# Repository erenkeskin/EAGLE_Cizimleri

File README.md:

# EAGLE_Cizimleri
AutoDesk Eagle PCB çizim programı ile çizdiğim çizimleri derlediğim depo

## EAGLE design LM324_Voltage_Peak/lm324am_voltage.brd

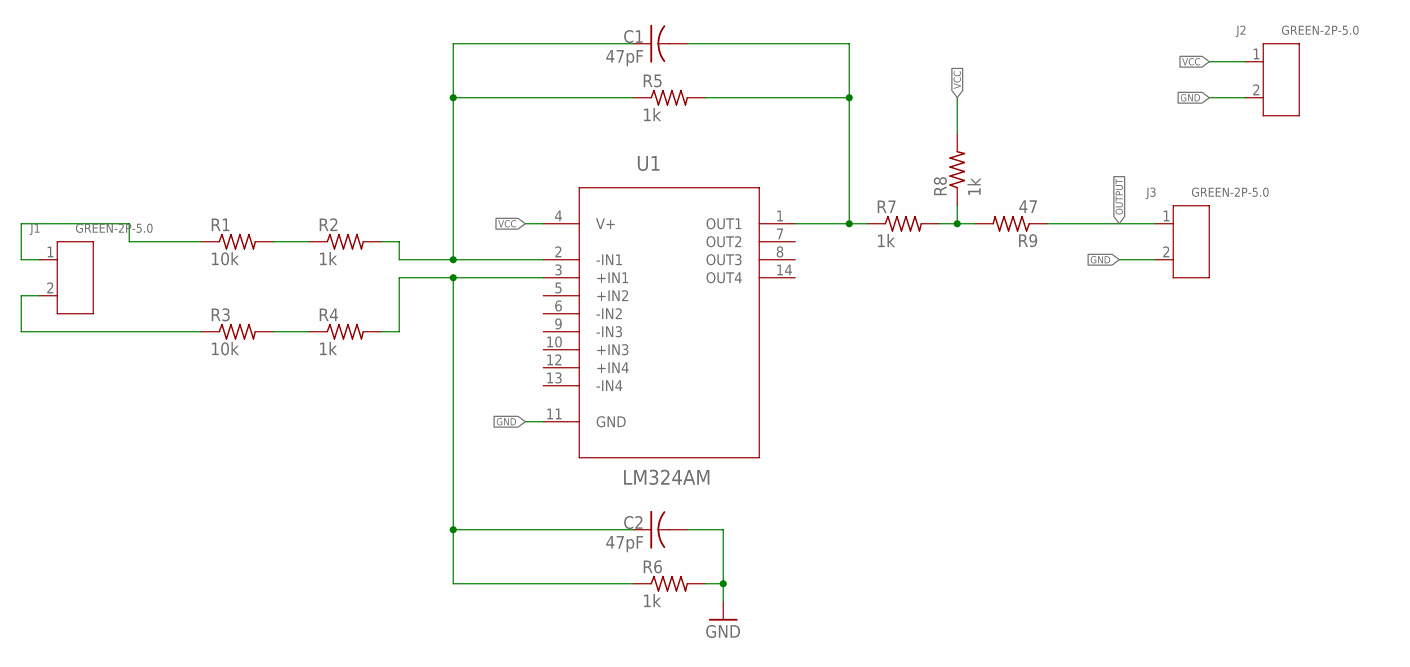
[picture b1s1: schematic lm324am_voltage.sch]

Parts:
C1, C2: 47pF; C1206
J1, J2, J3: GREEN-2P-5.0; H2-5.0-10.5X8.0MM
R1, R3: 10k; M1206
R2, R4, R5, R6, R7, R8: 1k; M1206
R9: 47; M1206
U1: LM324AM; SOIC127P620X175-14N

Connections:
GND: C2.2, J2.2, J3.2, R6.2, U1.11 (GND)
unnamed: J1.2, R3.1
unnamed: R3.2, R4.1
unnamed: R1.2, R2.1
unnamed: C1.1, R2.2, R5.1, U1.2 (-IN1)
unnamed: C2.1, R4.2, R6.1, U1.3 (+IN1)
unnamed: C1.2, R5.2, R7.1, U1.1 (OUT1)
unnamed: R7.2, R8.1, R9.2
unnamed: J1.1, R1.1
OUTPUT: J3.1, R9.1
VCC: J2.1, R8.2, U1.4 (V+)

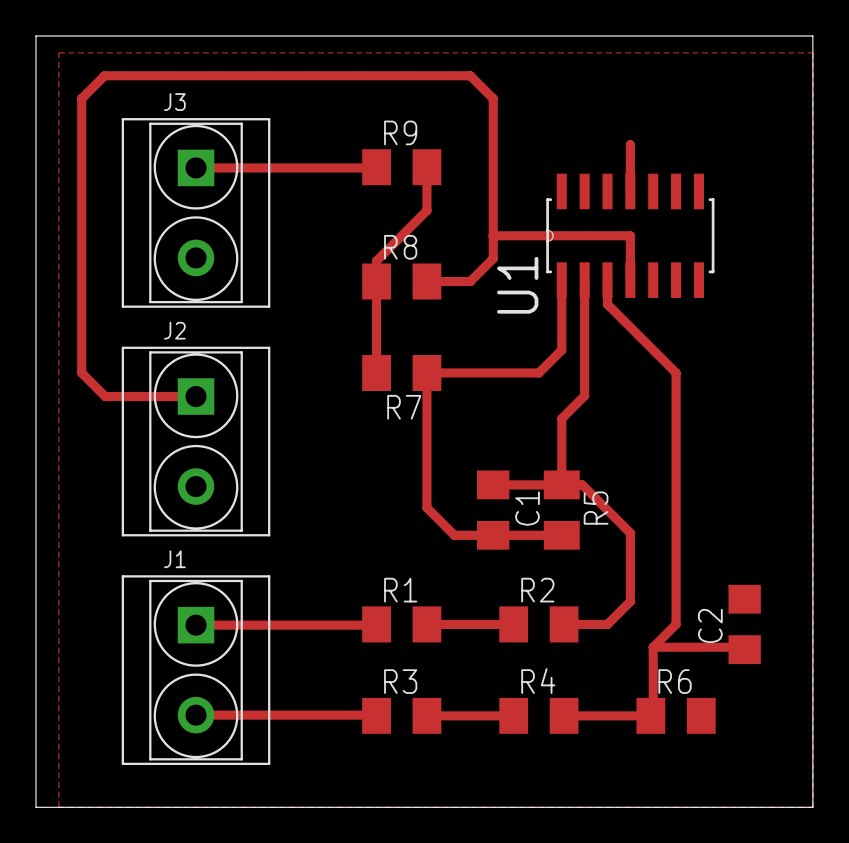
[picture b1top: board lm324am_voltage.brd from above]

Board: 2 copper layers, 43.2 x 42.9 mm, 15 parts (0 on the bottom side), 11 nets.

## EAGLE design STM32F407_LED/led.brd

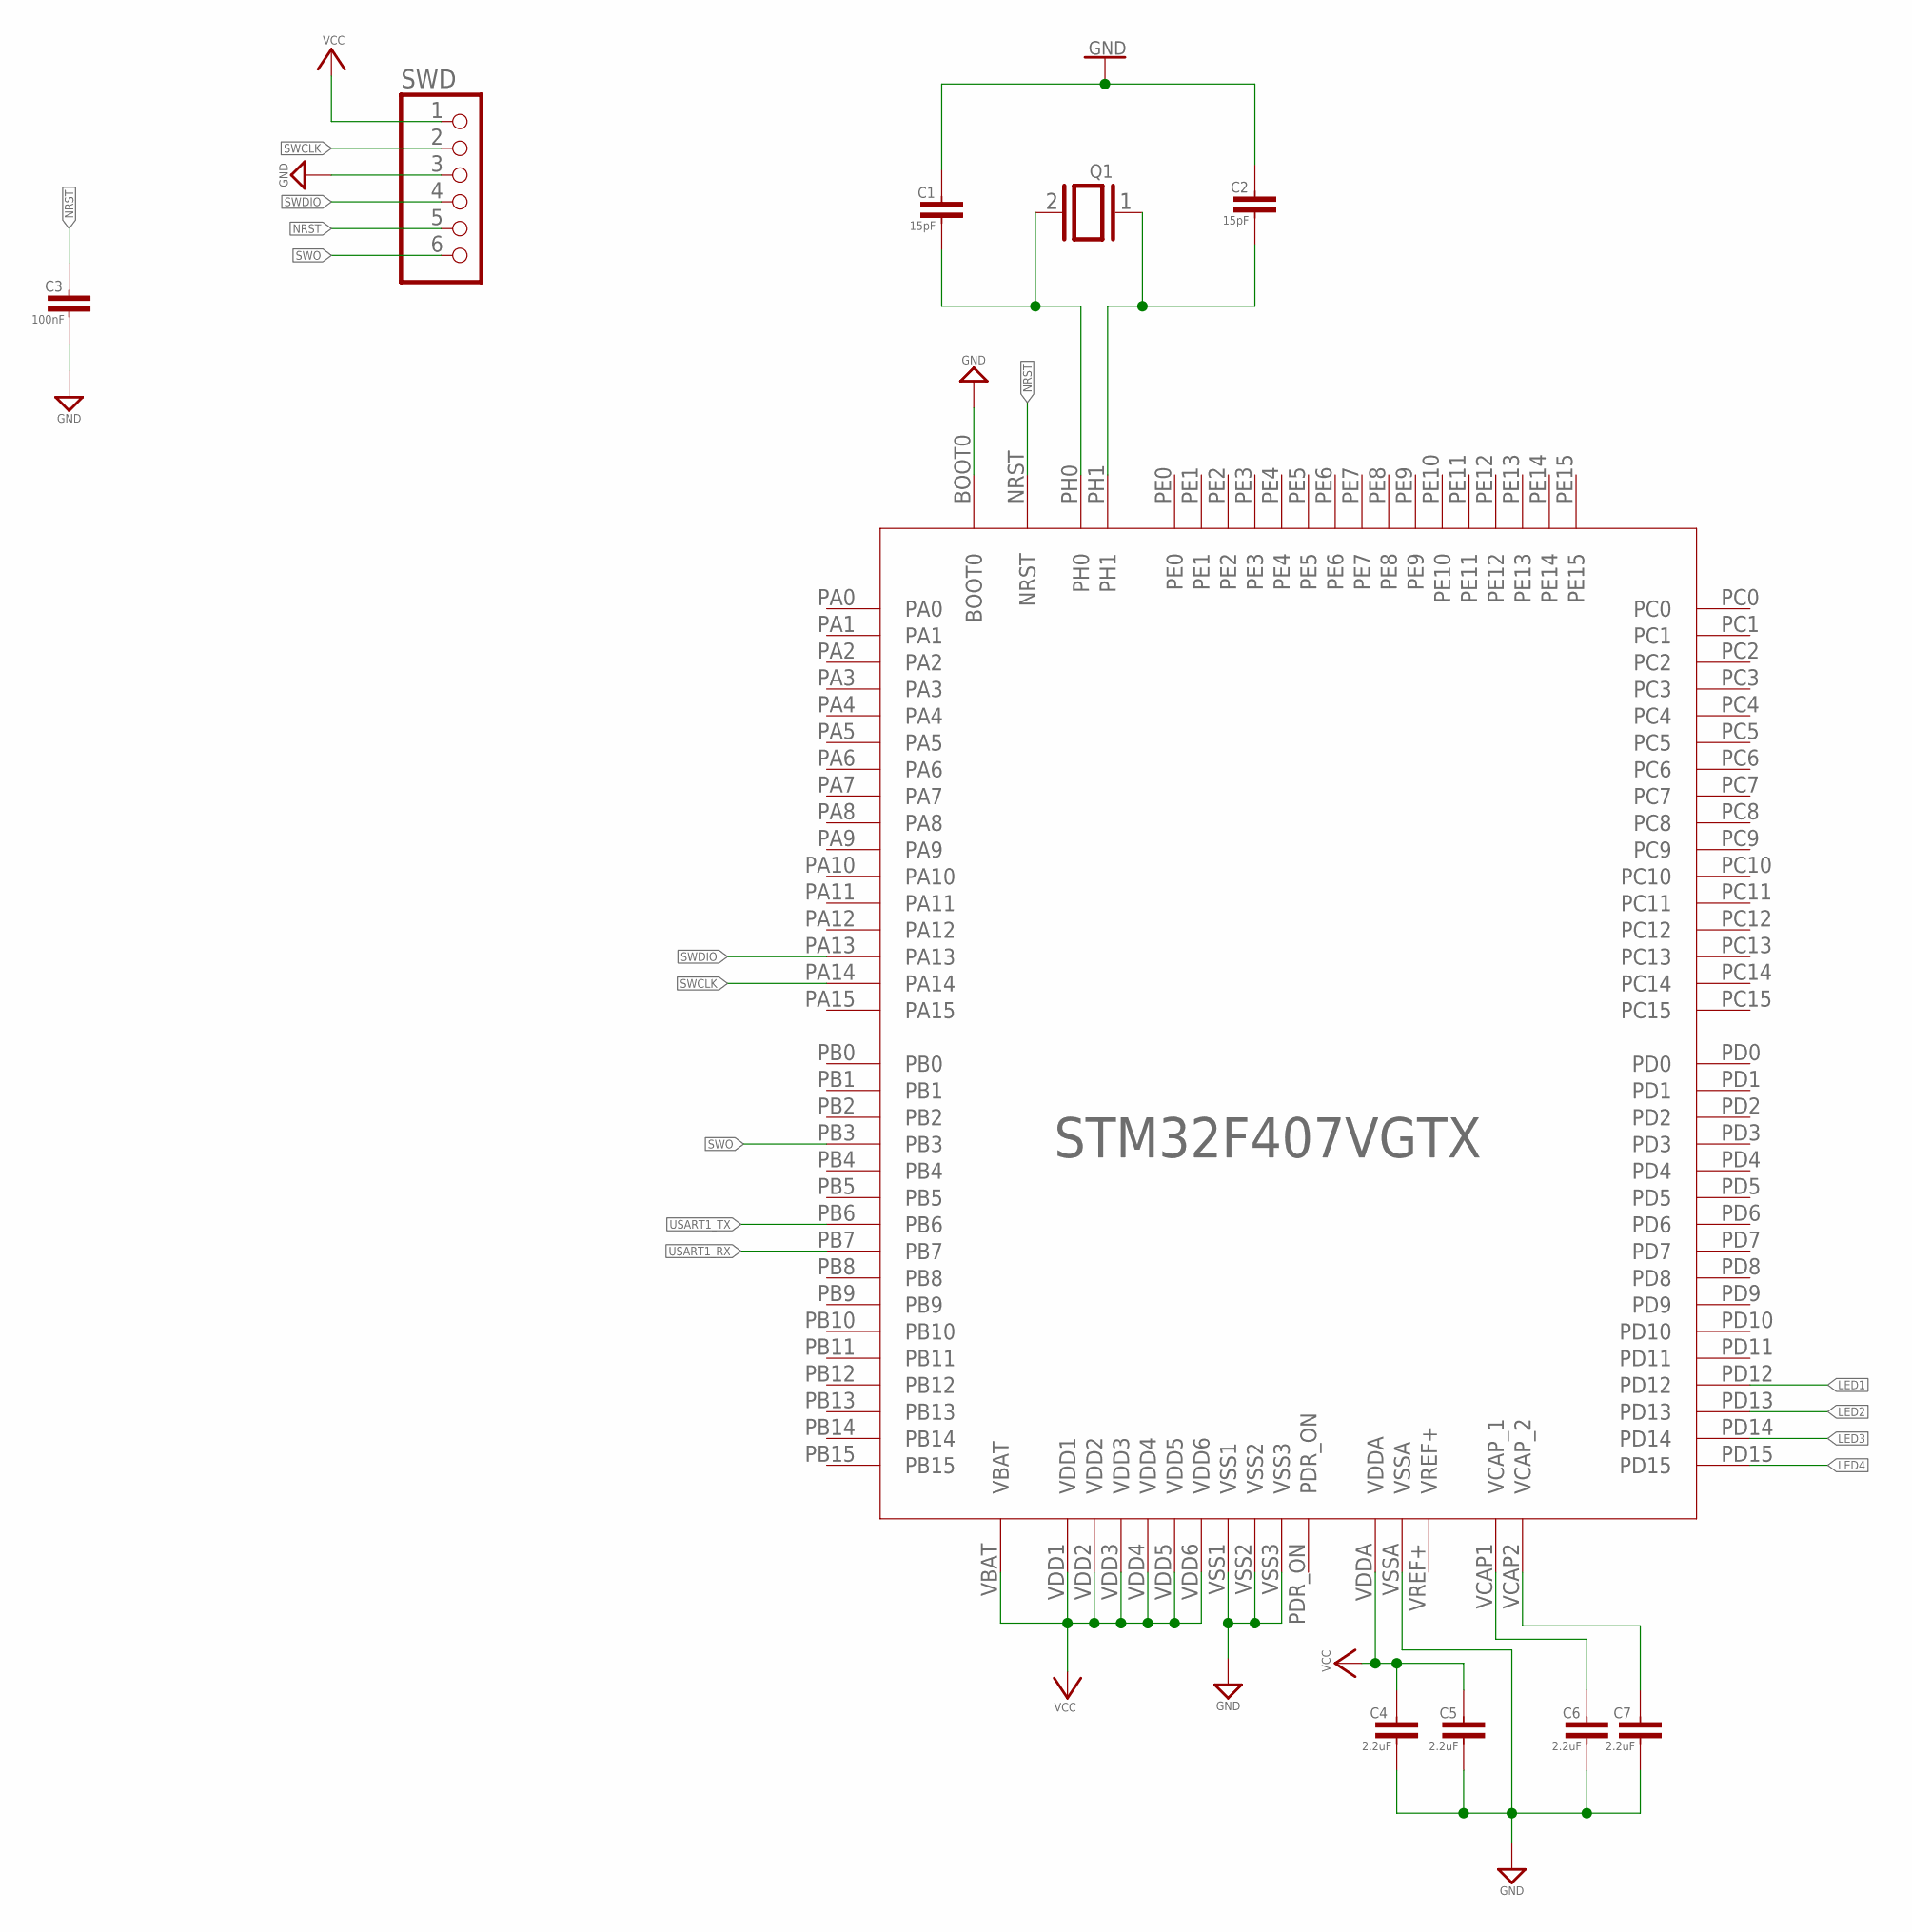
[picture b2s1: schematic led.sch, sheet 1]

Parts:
C1, C2: 15pF; C0603
C3: 100nF; C0603
C4, C5, C6, C7: 2.2uF; C0603
IC1: STM32F407VGTx; LQFP100
Q1: XTAL/S; QS
SWD: PINHD-1X6CB; 1X06-CLEANBIG

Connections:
GND: C1.1, C2.1, C3.2, C4.2, C5.2, C6.2, C7.2, IC1.BOOT0, IC1.VSS1, IC1.VSS2, IC1.VSS3, IC1.VSSA, SWD.3; also elsewhere on the board
LED1: IC1.PD12; also elsewhere on the board
LED2: IC1.PD13; also elsewhere on the board
LED3: IC1.PD14; also elsewhere on the board
LED4: IC1.PD15; also elsewhere on the board
unnamed: C2.2, IC1.PH1, Q1.1
unnamed: C1.2, IC1.PH0, Q1.2
unnamed: C6.1, IC1.VCAP1 (VCAP_1)
unnamed: C7.1, IC1.VCAP2 (VCAP_2)
NRST: C3.1, IC1.NRST, SWD.5
SWCLK: IC1.PA14, SWD.2
SWDIO: IC1.PA13, SWD.4
SWO: IC1.PB3, SWD.6
USART1_RX: IC1.PB7; also elsewhere on the board
USART1_TX: IC1.PB6; also elsewhere on the board
VCC: C4.1, C5.1, IC1.VBAT, IC1.VDD1, IC1.VDD2, IC1.VDD3, IC1.VDD4, IC1.VDD5, IC1.VDD6, IC1.VDDA, SWD.1; also elsewhere on the board

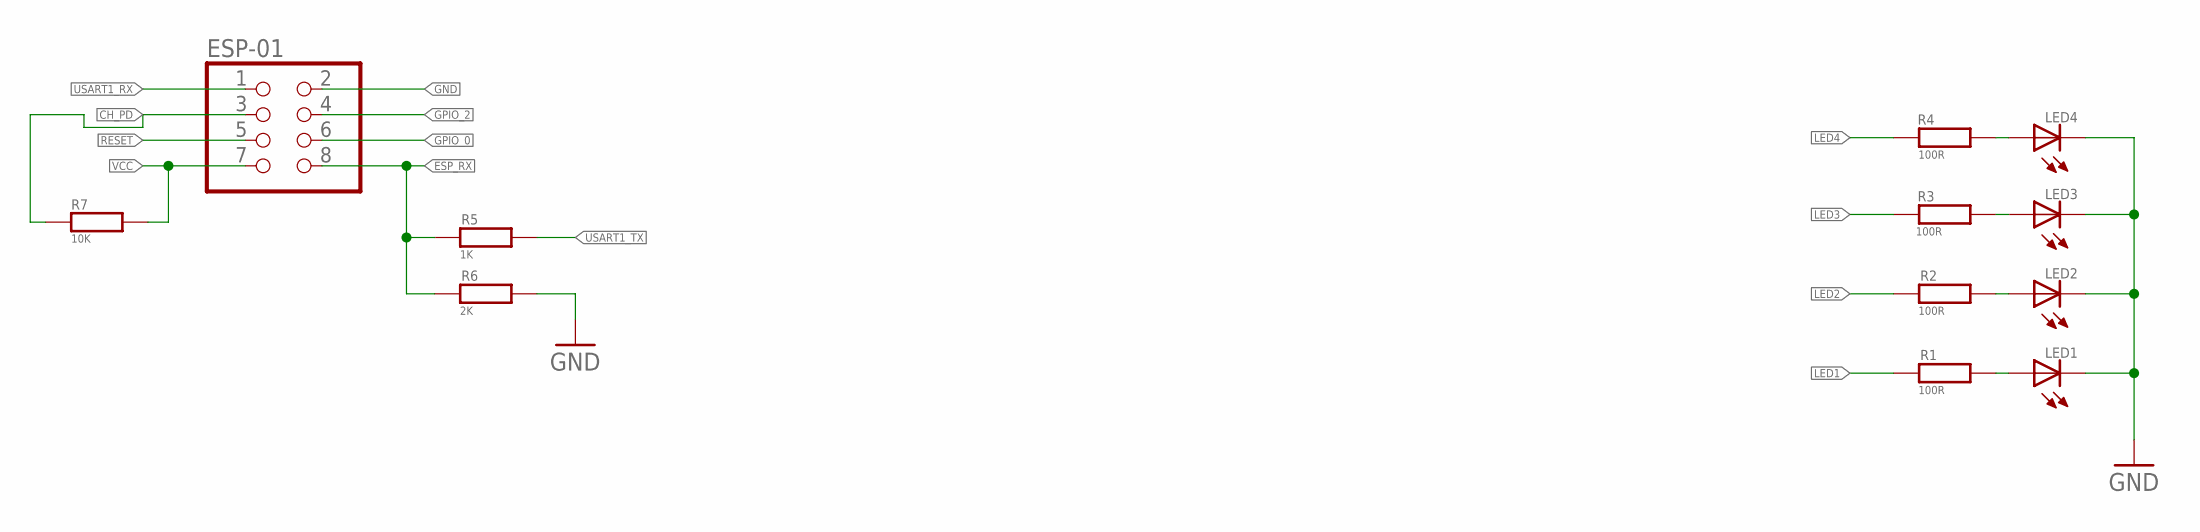
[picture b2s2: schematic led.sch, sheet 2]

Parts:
ESP-01: PINHD-2X4; 2X04
LED1, LED2, LED3, LED4: LEDCHIPLED_1206; CHIPLED_1206
R1, R2, R3, R4: 100R; R0603
R5: 1K; R0603
R6: 2K; R0603
R7: 10K; R0603

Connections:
CH_PD: ESP-01.3, R7.1
ESP_RX: ESP-01.8, R5.2, R6.2
GND: ESP-01.2, LED1.C, LED2.C, LED3.C, LED4.C, R6.1; also elsewhere on the board
GPIO_0: ESP-01.6
GPIO_2: ESP-01.4
LED1: R1.2; also elsewhere on the board
LED2: R2.2; also elsewhere on the board
LED3: R3.2; also elsewhere on the board
LED4: R4.2; also elsewhere on the board
unnamed: LED1.A, R1.1
unnamed: LED2.A, R2.1
unnamed: LED3.A, R3.1
unnamed: LED4.A, R4.1
RESET: ESP-01.5
USART1_RX: ESP-01.1; also elsewhere on the board
USART1_TX: R5.1; also elsewhere on the board
VCC: ESP-01.7, R7.2; also elsewhere on the board

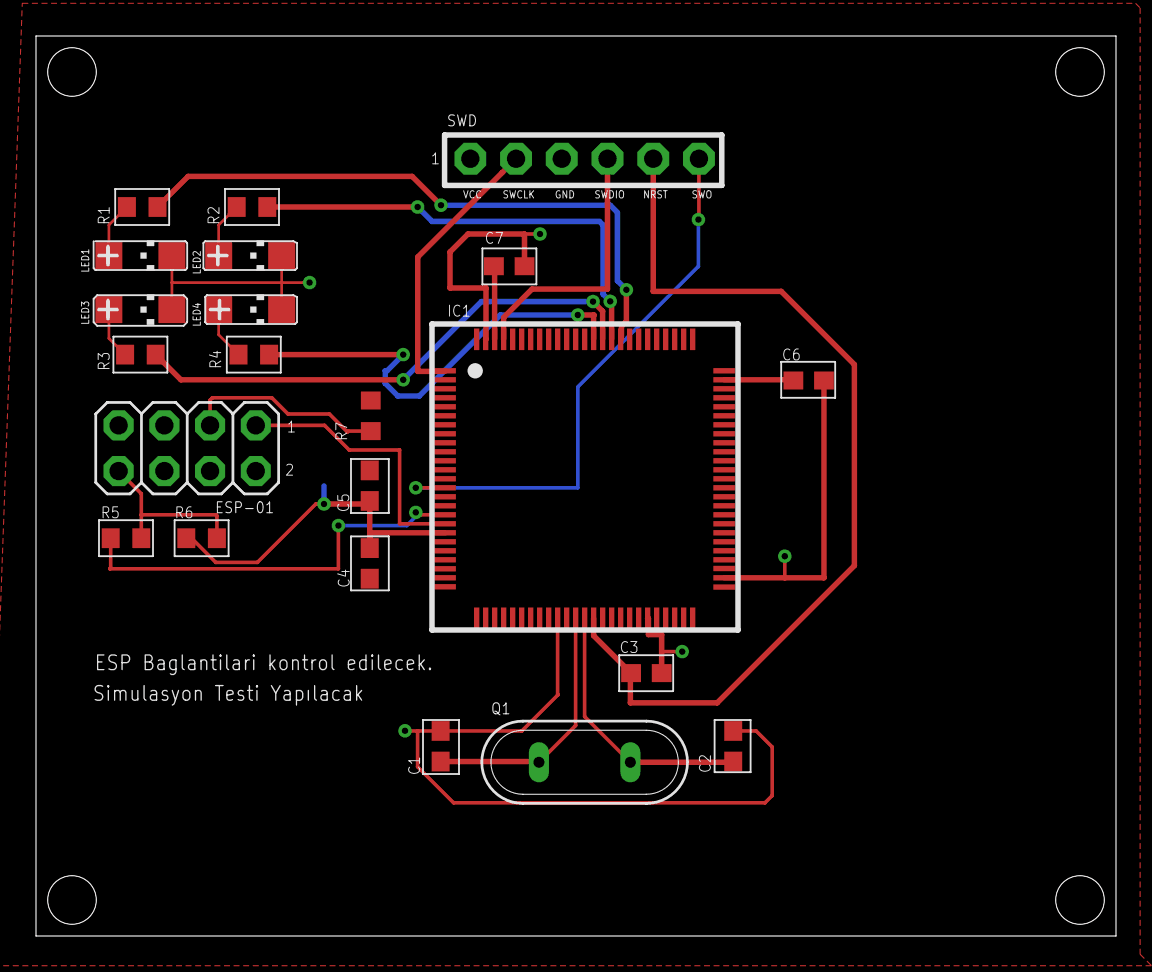
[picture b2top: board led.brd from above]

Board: 2 copper layers, 60.0 x 50.0 mm, 22 parts (0 on the bottom side), 22 nets.

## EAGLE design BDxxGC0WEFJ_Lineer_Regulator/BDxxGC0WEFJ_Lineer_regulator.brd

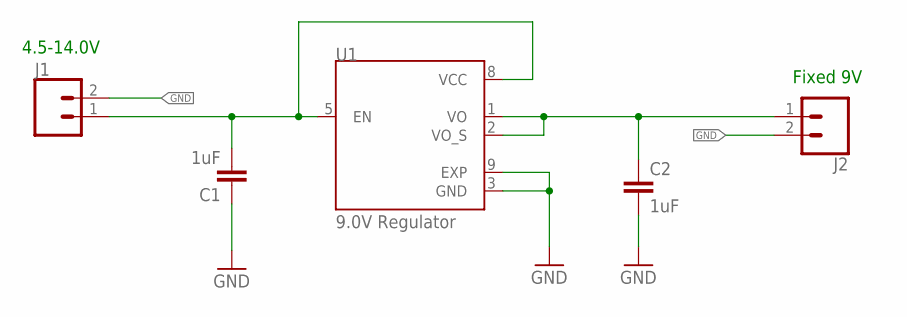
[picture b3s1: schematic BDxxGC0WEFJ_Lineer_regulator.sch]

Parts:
C1, C2: 1uF; C0603
J1, J2: CONN_02; 1X02
U1: 9.0V Regulator; SOIC127P600X100-9N

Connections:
GND: C1.1, C2.2, J1.2, J2.2, U1.3 (GND), U1.9 (EXP)
unnamed: C1.2, J1.1, U1.5 (EN), U1.8 (VCC)
unnamed: C2.1, J2.1, U1.1 (VO), U1.2 (VO_S)

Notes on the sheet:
4.5-14.0V
Fixed 9V

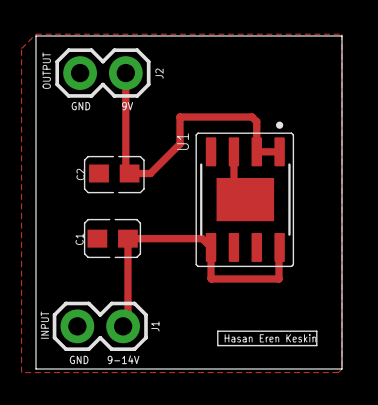
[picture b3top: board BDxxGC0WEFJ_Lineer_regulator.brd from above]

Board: 2 copper layers, 17.0 x 18.5 mm, 5 parts (0 on the bottom side), 3 nets.

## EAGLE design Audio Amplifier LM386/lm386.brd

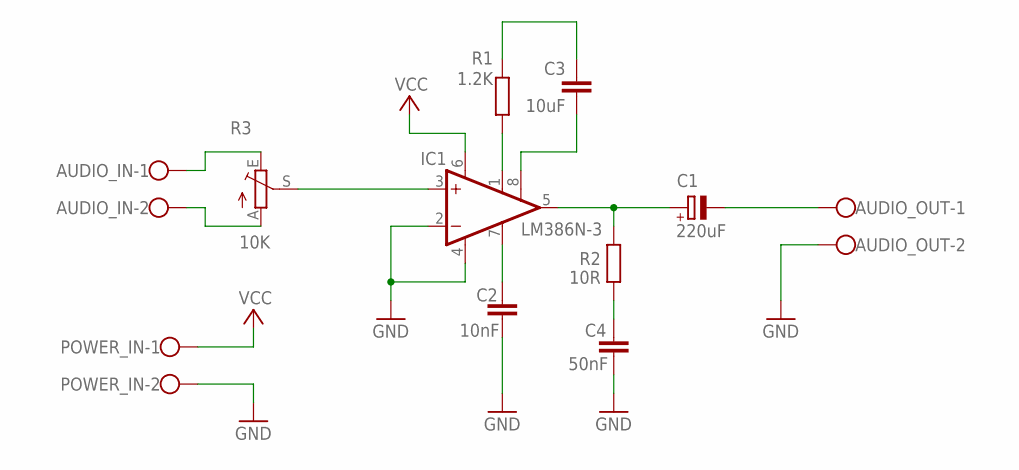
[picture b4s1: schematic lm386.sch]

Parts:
AUDIO_IN: W237-102
AUDIO_OUT: W237-102
C1: 220uF; E3,5-8
C2: 10nF; C025-025X050
C3: 10uF; C075-032X103
C4: 50nF; C025-025X050
IC1: LM386N-3; DIL08
POWER_IN: W237-102
R1: 1.2K; 0204/7
R2: 10R; 0204/7
R3: 10K; B64Y

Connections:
GND: AUDIO_OUT.2, C2.1, C4.2, IC1.2 (-IN), IC1.4 (GND), POWER_IN.2
unnamed: AUDIO_IN.1, R3.E
unnamed: AUDIO_IN.2, R3.A
unnamed: IC1.3 (+IN), R3.S
unnamed: C2.2, IC1.7 (BYPASS)
unnamed: C1.+, IC1.5 (OUT), R2.2
unnamed: C4.1, R2.1
unnamed: AUDIO_OUT.1, C1.-
unnamed: C3.1, IC1.8 (GAIN)
unnamed: C3.2, R1.2
unnamed: IC1.1 (GAIN), R1.1
VCC: IC1.6 (VS), POWER_IN.1

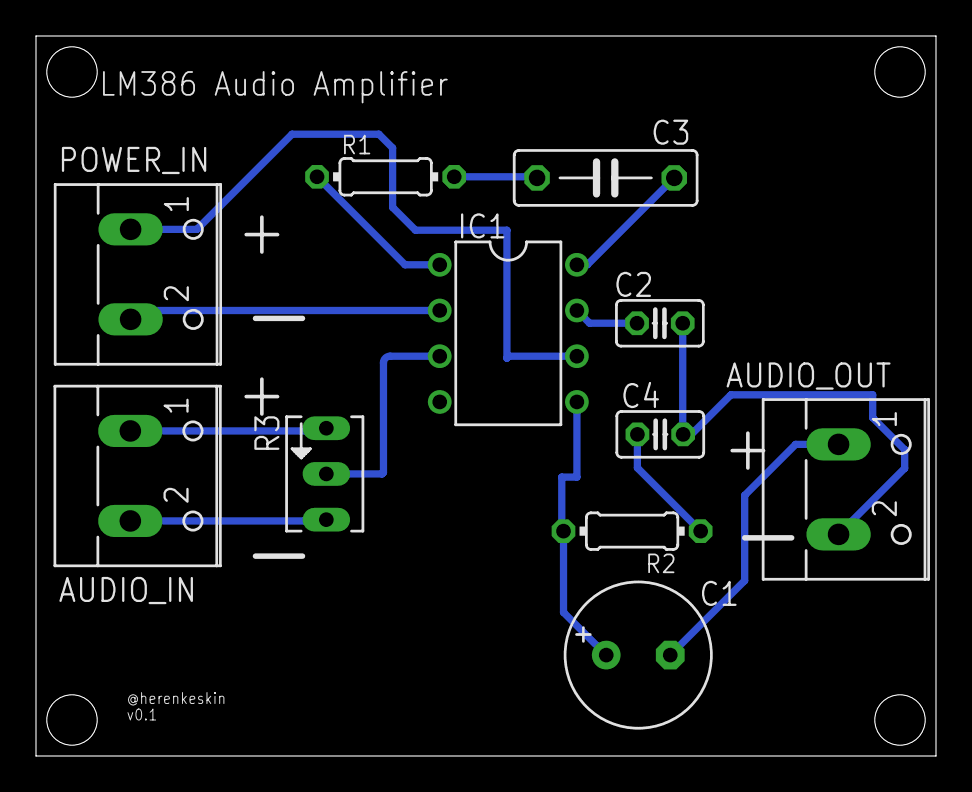
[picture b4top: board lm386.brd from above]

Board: 2 copper layers, 50.0 x 40.0 mm, 11 parts (0 on the bottom side), 12 nets.

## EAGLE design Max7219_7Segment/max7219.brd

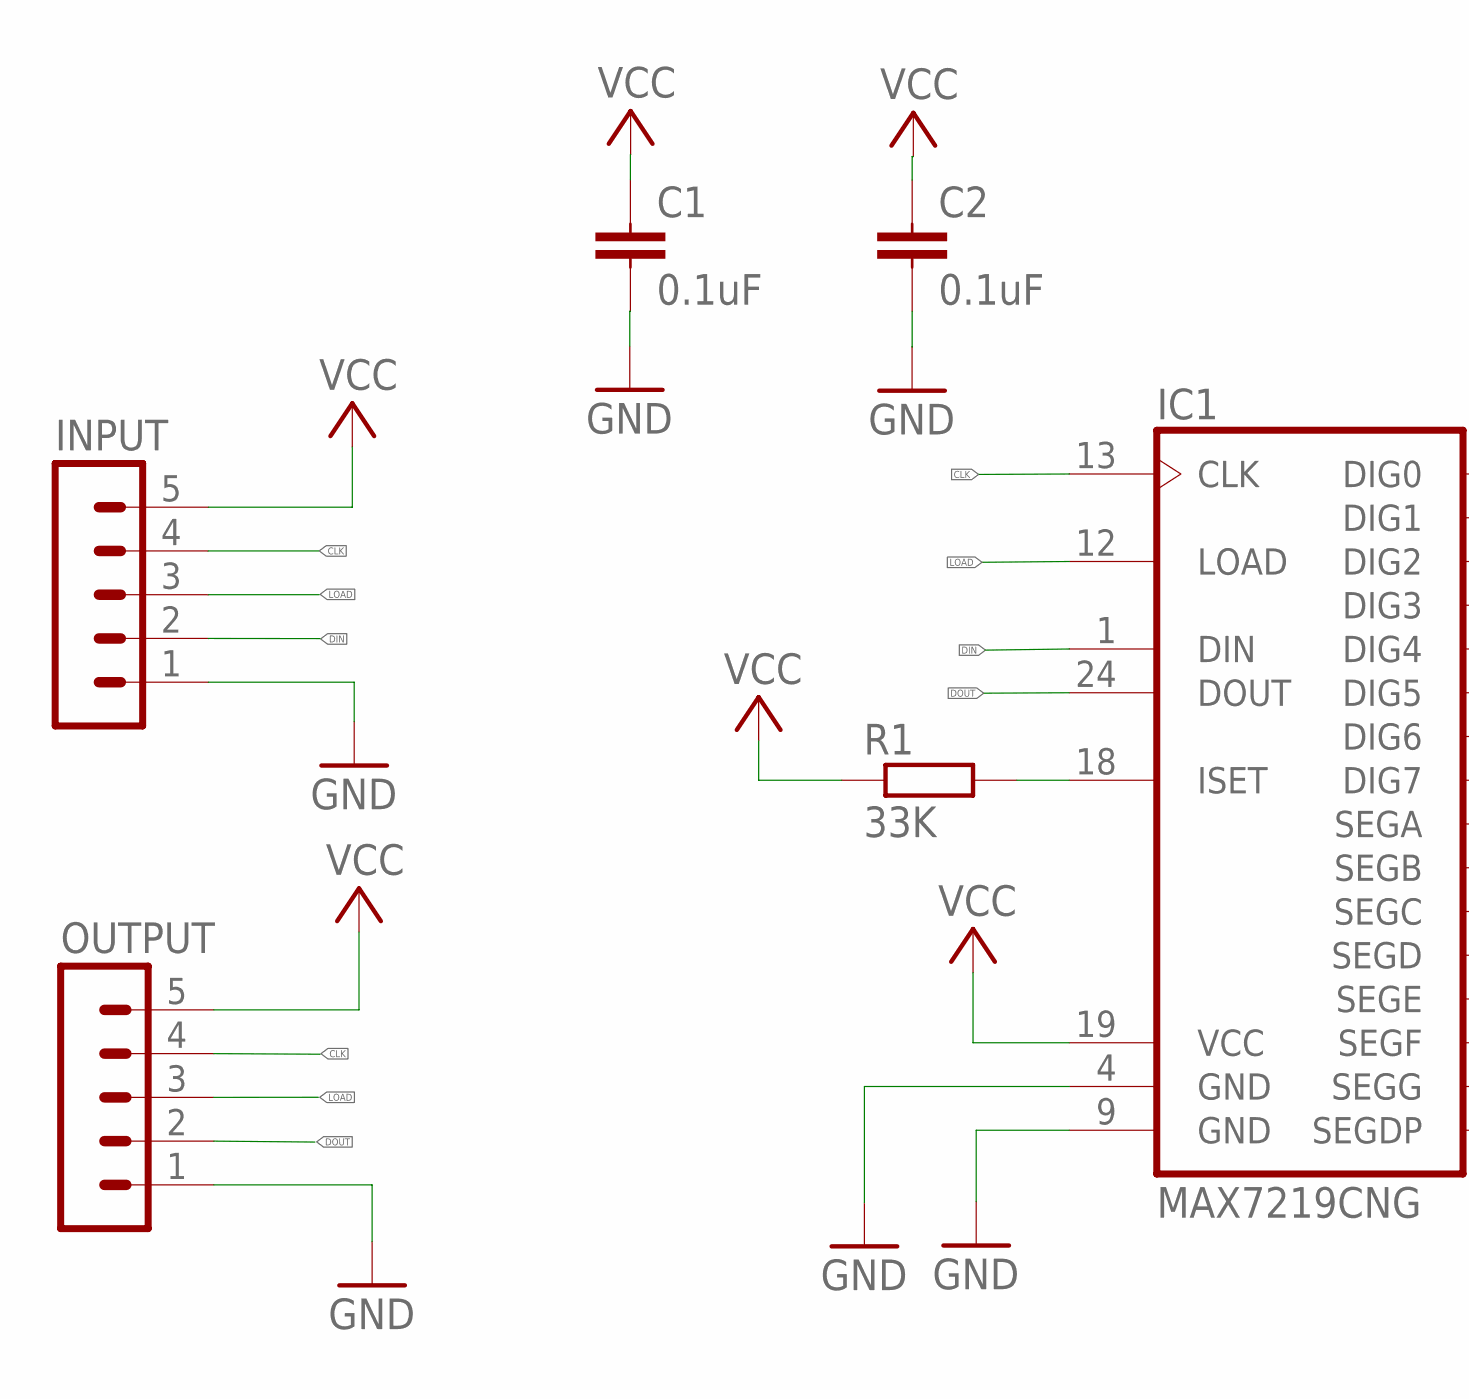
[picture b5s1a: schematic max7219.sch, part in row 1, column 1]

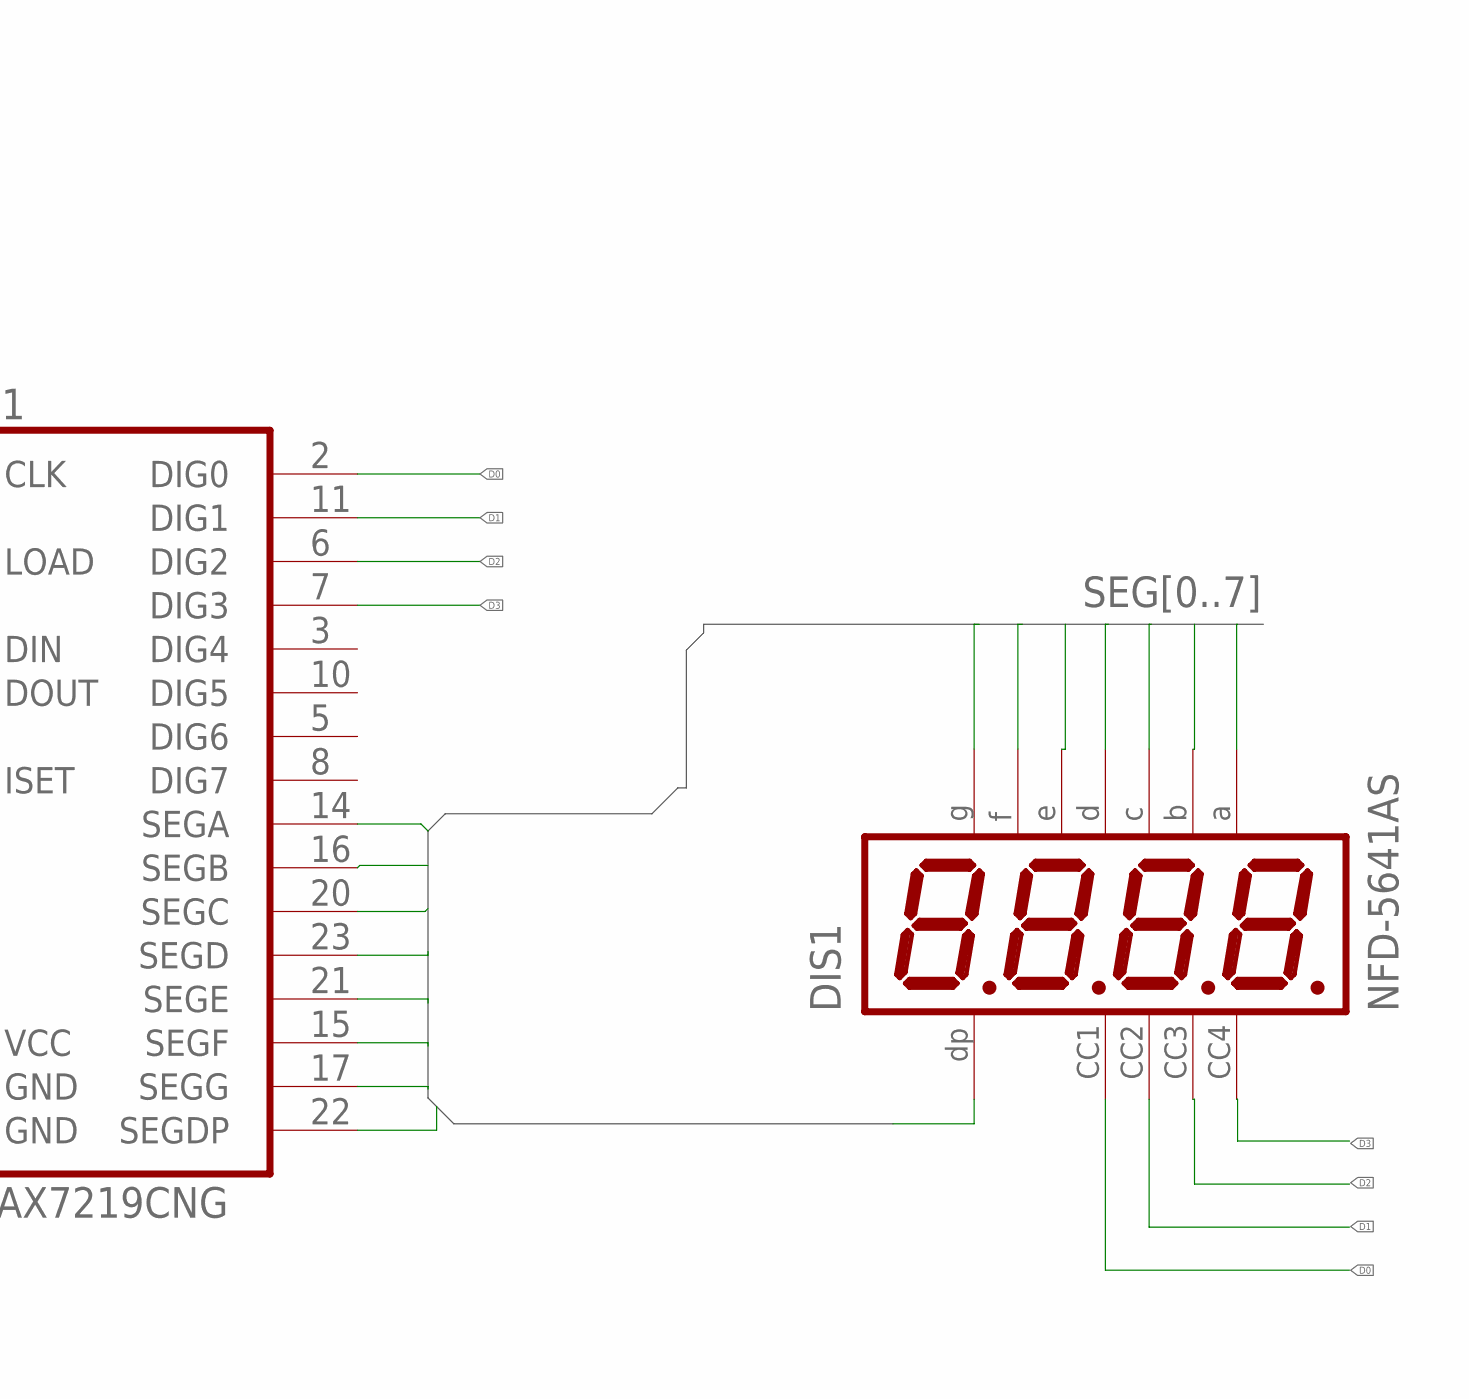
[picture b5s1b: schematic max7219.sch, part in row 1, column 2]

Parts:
C1, C2: 0.1uF; C025-025X050
DIS1: NFD-5641AS; NFD-5641
IC1: MAX7219CNG; DIL24-3
INPUT: MA05-1
OUTPUT: MA05-1
R1: 33K; 0207/10

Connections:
CLK: IC1.13 (CLK), INPUT.4, OUTPUT.4
D0: DIS1.P$12, IC1.2 (DIG0)
D1: DIS1.P$9, IC1.11 (DIG1)
D2: DIS1.P$8, IC1.6 (DIG2)
D3: DIS1.P$6, IC1.7 (DIG3)
DIN: IC1.1 (DIN), INPUT.2
DOUT: IC1.24 (DOUT), OUTPUT.2
GND: C1.2, C2.2, IC1.4 (GND), IC1.9 (GND), INPUT.1, OUTPUT.1
LOAD: IC1.12 (LOAD), INPUT.3, OUTPUT.3
unnamed: IC1.18 (ISET), R1.2
SEG0: DIS1.P$11, IC1.14 (SEGA)
SEG1: DIS1.P$7, IC1.16 (SEGB)
SEG2: DIS1.P$4, IC1.20 (SEGC)
SEG3: DIS1.P$2, IC1.23 (SEGD)
SEG4: DIS1.P$1, IC1.21 (SEGE)
SEG5: DIS1.P$10, IC1.15 (SEGF)
SEG6: DIS1.P$5, IC1.17 (SEGG)
SEG7: DIS1.P$3, IC1.22 (SEGDP)
VCC: C1.1, C2.1, IC1.19 (VCC), INPUT.5, OUTPUT.5, R1.1

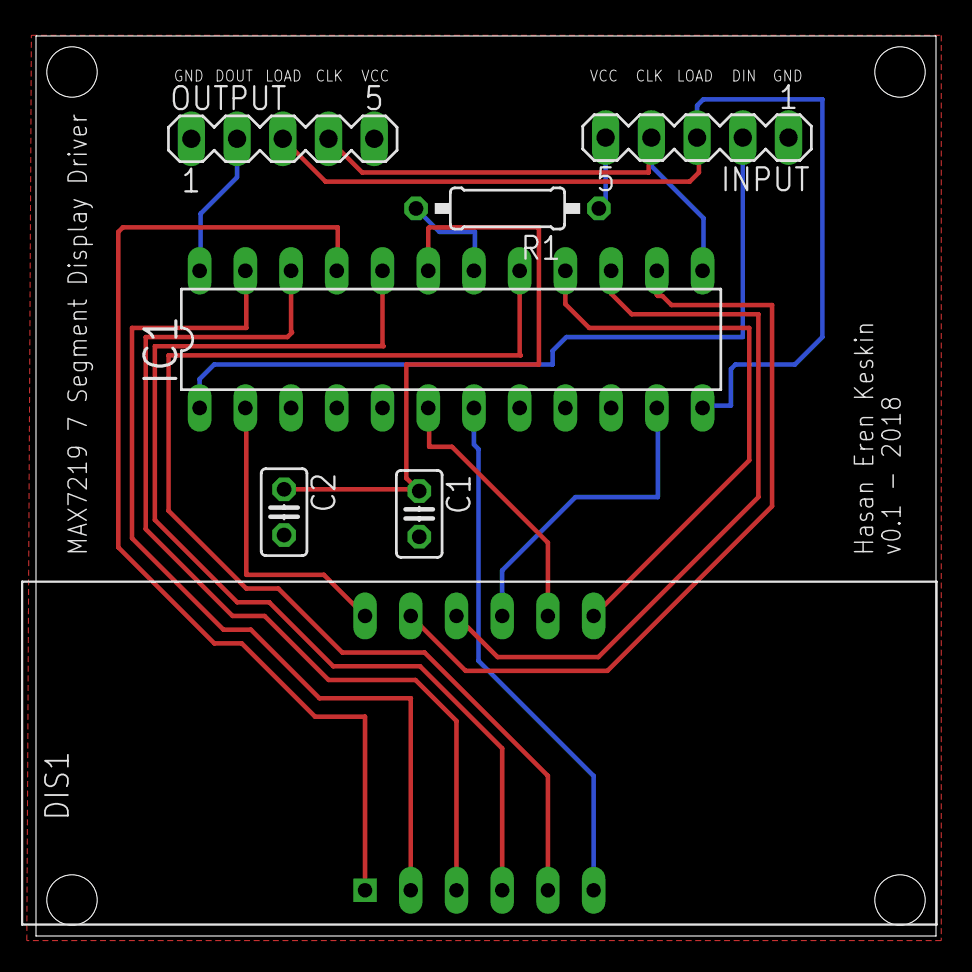
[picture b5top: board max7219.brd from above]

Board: 2 copper layers, 50.0 x 50.0 mm, 7 parts (0 on the bottom side), 19 nets.

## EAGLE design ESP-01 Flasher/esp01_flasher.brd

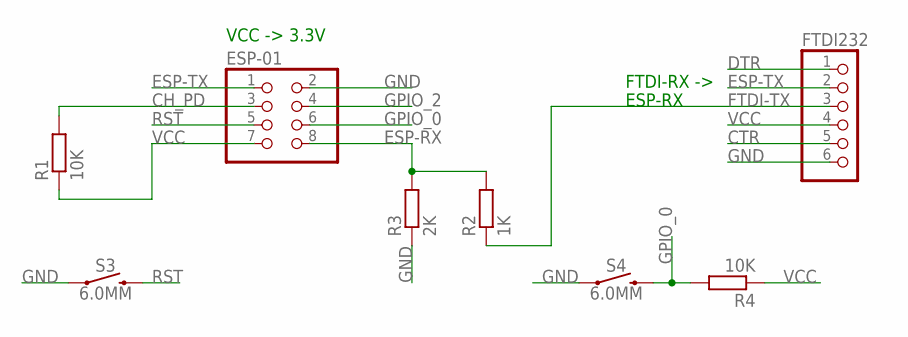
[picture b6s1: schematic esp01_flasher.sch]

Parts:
ESP-01: PINHD-2X4; 2X04
FTDI232: PINHD-1X6; 1X06
R1, R4: 10K; R1206
R2: 1K; R1206
R3: 2K; R1206
S3, S4: 6.0MM; TACTILE_SWITCH_PTH_6.0MM

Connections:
CH_PD: ESP-01.3, R1.2
CTR: FTDI232.5
DTR: FTDI232.1
ESP-RX: ESP-01.8, R2.2, R3.2
ESP-TX: ESP-01.1, FTDI232.2
FTDI-TX: FTDI232.3, R2.1
GND: ESP-01.2, FTDI232.6, R3.1, S3.1, S4.1
GPIO_0: ESP-01.6, R4.2, S4.3 (2)
GPIO_2: ESP-01.4
RST: ESP-01.5, S3.3 (2)
VCC: ESP-01.7, FTDI232.4, R1.1, R4.1

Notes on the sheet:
VCC -> 3.3V
FTDI-RX ->
ESP-RX

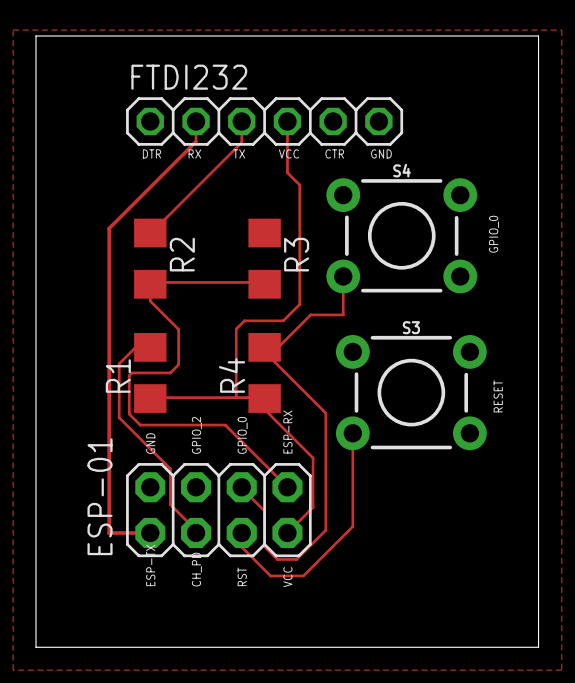
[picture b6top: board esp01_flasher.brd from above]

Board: 2 copper layers, 27.9 x 34.0 mm, 8 parts (0 on the bottom side), 8 nets.

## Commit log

2018-10-14 ESP-01 Flasher
2018-10-14 ESP-01 Flasher v0.2
2018-10-28 7 Segment Display Driver
2018-10-28 LM386 Audio Amplifier
2018-10-28 7 Segment Display Driver Views Added
2018-10-28 LM386 Audio Amplifier Views Added
2018-10-31 BDxxGC0WEFJ_Lineer_Regulator Added
2018-11-10 STM32F407 Led and ESP8266
2018-12-01 STM32F103 First
2019-02-14 Sinyal verileri alindi
2019-03-10 LM324AM Voltage Peak Detected

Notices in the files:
parts and their libraries:
SparkFun-Connectors: Licensing: Creative Commons ShareAlike 4.0 International - https://creativecommons.org/licenses/by-sa/4.0
